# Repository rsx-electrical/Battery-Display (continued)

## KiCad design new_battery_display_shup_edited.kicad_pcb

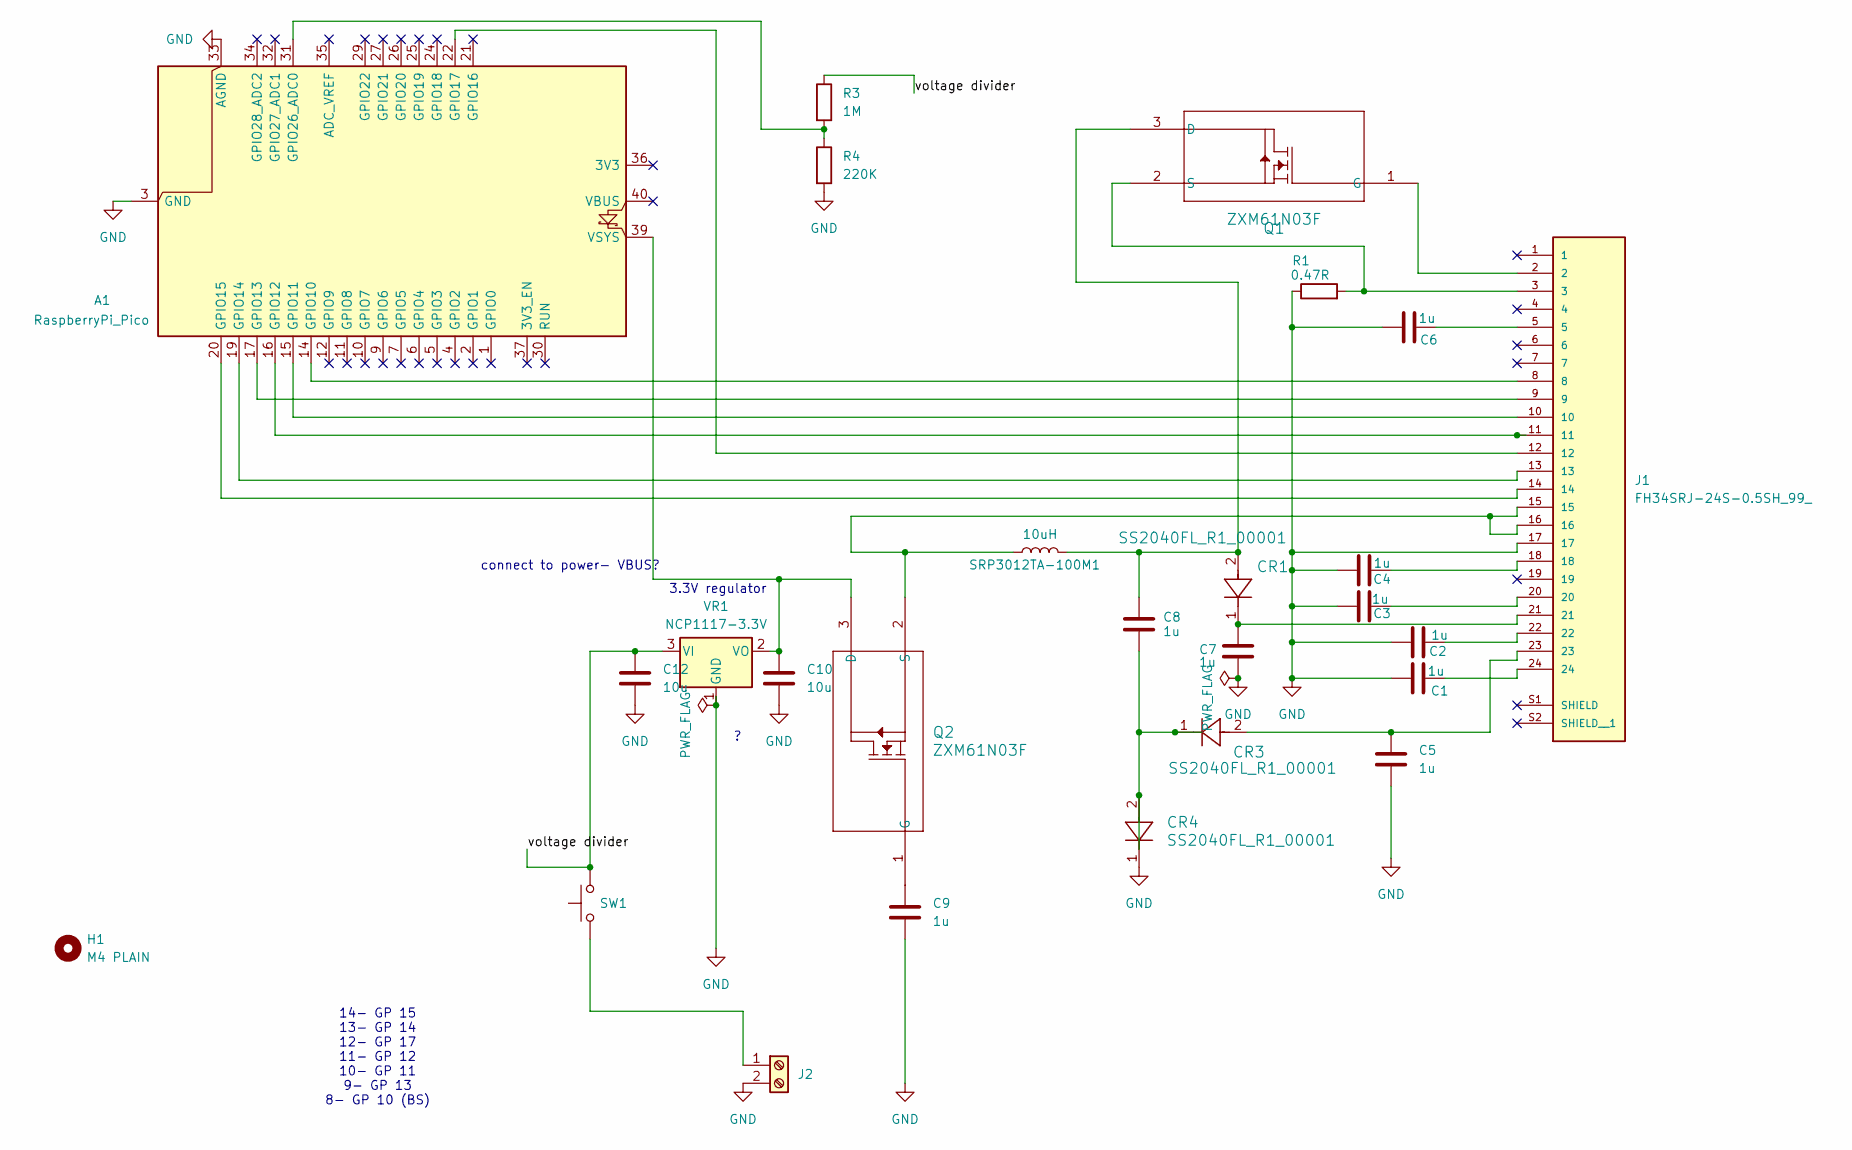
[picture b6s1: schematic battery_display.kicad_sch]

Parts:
A1: RaspberryPi_Pico; RaspberryPi_Pico_Common_Unspecified
C1, C2, C3, C4, C5, C6, C7, C8, C9: 1u; C_0805_2012Metric; MPN CL21B105KBFNNNE
C10, C12: 10u; C_0805_2012Metric; MPN GRM21BR61H106KE43L
CR1, CR3, CR4: SS2040FL_R1_00001; Nexperia_CFP3_SOD-123W; MPN SS2040FL_R1_00001
H1: M4 PLAIN; MountingHole_4.5mm
J1: FH34SRJ-24S-0.5SH_99_; HRS_FH34SRJ-24S-0.5SH_99_; PARTREV NA
J2: Screw_Terminal_2x2.54; Wurth_691210910002; MPN 691210910002
Q1, Q2: ZXM61N03F; SOT-23; MPN ZXM61N03FTA
R1: 0.47R; R_1206_3216Metric; MPN RL1206FR-070R47L
R3: 1M; R_0603_1608Metric; MPN ERJ-3EKF1004V
R4: 220K; R_0603_1608Metric; MPN RMCF0603FT220K
SRP3012TA-100M1: 10uH; IND_SRP3012TA_BRN; MPN SRP3012TA-100M
SW1: Button-THT - 2-1825910-7; 2-1825910-7; MPN 2-1825910-7
VR1: NCP1117-3.3V; SOT-223-3_TabPin2; MPN NCP1117IST33T3G

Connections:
/voltage divider: C12.1, R3.1, SW1.2, VR1.3 (VI)
GND: A1.3 (GND), A1.8 (GND), A1.13 (GND), A1.18 (GND), A1.23 (GND), A1.28 (GND), A1.33 (AGND), A1.38 (GND), C1.1, C2.1, C3.1, C4.1, C5.2, C6.1, C7.1, C9.1, C10.2, C12.2, CR4.1, J1.17, J2.2, R1.1, R4.2, VR1.1 (GND); also elsewhere on the board
unnamed: A1.14 (GPIO10), J1.8
unnamed: A1.15 (GPIO11), J1.10
unnamed: A1.16 (GPIO12), J1.11
unnamed: A1.17 (GPIO13), J1.9
unnamed: A1.19 (GPIO14), J1.13
unnamed: A1.20 (GPIO15), J1.14
unnamed: A1.22 (GPIO17), J1.12
unnamed: A1.31 (GPIO26_ADC0), R3.2, R4.1
unnamed: A1.39 (VSYS), C10.1, Q2.3 (D), VR1.2 (VO)
unnamed: C1.2, J1.24
unnamed: C2.2, J1.22
unnamed: C3.2, J1.20
unnamed: C4.2, J1.18
unnamed: C5.1, CR3.2, J1.23
unnamed: C6.2, J1.5
unnamed: C7.2, CR1.1, J1.21
unnamed: C8.1, CR3.1, CR4.2
unnamed: J2.1, SW1.1
unnamed 20: C8.2, CR1.2, Q1.3 (D), SRP3012TA-100M1.2; also elsewhere on the board
unnamed 21: J1.2, Q1.1 (G); also elsewhere on the board
unnamed: J1.3, Q1.2 (S), R1.2
unnamed: C9.2, Q2.1 (G)
unnamed: J1.15, J1.16, Q2.2 (S), SRP3012TA-100M1.1

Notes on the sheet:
3.3V regulator
connect to power- VBUS?
14- GP 15 13- GP 14 12- GP 17 11- GP 12 10- GP 11 9- GP 13 8- GP 10 (BS)

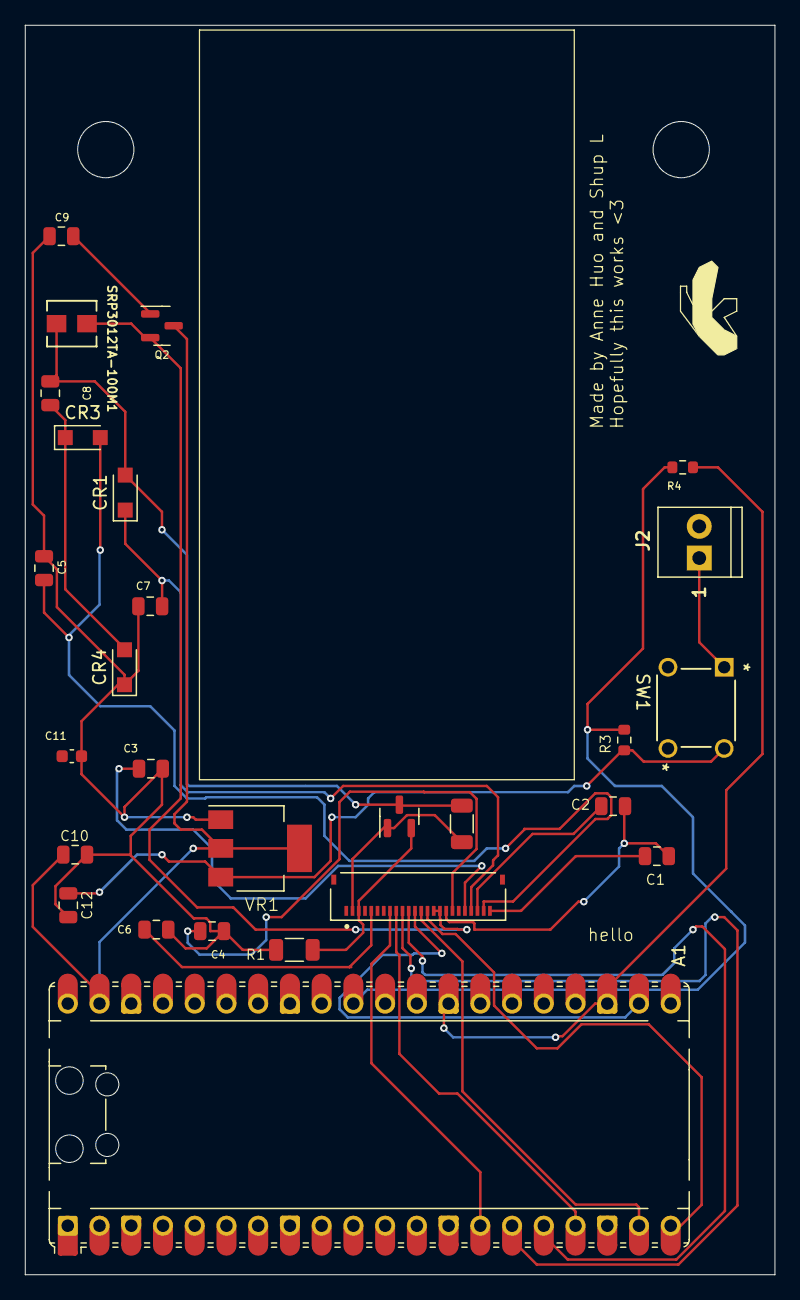
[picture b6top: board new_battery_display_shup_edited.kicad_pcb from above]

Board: 2 copper layers, 60.0 x 100.0 mm, 29 parts (0 on the bottom side), 25 nets.

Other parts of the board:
C11: 0u1; C_0603_1608Metric
H1#2: M4 PLAIN; MountingHole_4.5mm
R2: 0.47R; R_1206_3216Metric

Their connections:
GND: C11.2; also elsewhere on the board
unnamed 20: R2.1; also elsewhere on the board
unnamed 21: R2.2; also elsewhere on the board

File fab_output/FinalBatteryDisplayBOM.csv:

"Id";"Designator";"Footprint";"Quantity";"Designation";"Supplier and ref";
1;"C3,C5,C9,C8,C2,C6,C4,C1";"C_0805_2012Metric";8;"1u";;;
2;"J1";"HRS_FH34SRJ-24S-0.5SH_99_";1;"FH34SRJ-24S-0.5SH_99_";;;
3;"C10,C7";"C_0805_2012Metric";2;"10u";;;
4;"Q2";"SOT-23";1;"ZXM61N03F";;;
5;"R6";"R_0603_1608Metric";1;"249K_0.1%";;;
6;"C13";"C_0603_1608Metric";1;"0u1";;;
7;"R2";"R_1206_3216Metric";1;"0.47R";;;
8;"CR1,CR2,CR3";"Nexperia_CFP3_SOD-123W";3;"SS2040FL_R1_00001";;;
9;"VR1";"SOT-223-3_TabPin2";1;"NCP1117-3.3V";;;
10;"J2";"Wurth_691210910002";1;"Screw_Terminal_2x2.54";;;
11;"SW1";"FSMSMTR";1;"Button";;;
12;"I1-SRP";"IND_SRP3012TA_BRN";1;"10uH";;;
13;"A2";"RaspberryPi_Pico_Common_Unspecified";1;"RaspberryPi_Pico";;;
14;"C12";"C_0805_2012Metric";1;"4u7";;;
15;"R7";"R_0603_1608Metric";1;"1M";;;

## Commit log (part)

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2025-09-06 Created Shopping List
2025-09-06 Updated Shopping List Formmating
2025-09-16 add screen
2025-09-16 nmos
2025-09-16 alexmos
2025-09-24 add ldo
2025-09-28 shopping list 3v3 ldo
2025-10-04 add kicad project
2025-10-04 Started schematic
2025-10-04 EndofOct4
2025-10-11 Oct11_Schematic
2025-10-11 Add EPD library
2025-10-18 update schematic with 2 diodes
2025-10-18 display kicad schematic
2025-10-18 what the heklly
2025-10-18 2nd display
2025-10-18 added pico help
    asd
2025-10-18 display
2025-10-18 Create oct 18
2025-10-19 removed unnecessary mosfet in list
2025-10-19 Revert "removed unnecessary mosfet in list"
    This reverts commit 033c1a85e05191d0f7b3fb11770f73466afdf9e2.
2025-10-19 removed useless mosfet
2025-10-19 started battery display schematic
2025-10-19 Create fp-info-cache
2025-10-25 add button
2025-10-25 add button 2
2025-10-25 add pico pinout pic
2025-10-25 Schematic in progress
    added base schematic
    -next steps:
    -add connections to rpi pico
    -find values for soft start
2025-10-25 updated library links
2025-11-01 arduino w/ new components project folder added
2025-11-01 new project folders for new arduino and new comps vers
2025-11-01 Add progress so far
2025-11-01 Nano every
2025-11-01 Schematic with Pico
2025-11-01 Pico connected to display (mostly???)
2025-11-01 Display + Pico + voltage regulator
2025-11-08 Nov8 update
2025-11-08 11/08/25
2025-11-08 fixed
2025-11-08 title
2025-11-08 fixed changes
2025-11-08 new voltage regulator
2025-11-09 nov 8th changed back to raspberry pico
2025-11-15 i hate git: added voltage divider, added pwr flag
2025-11-15 added stuff:
    biuiuhiu
2025-11-15 Nov 15 schematic
2025-11-22 added new stuff:slow start
2025-11-22 remove op amp, used voltage divider with 1M resistor
2025-11-22 Nov22
2025-11-22 i made a new project titled yey. it is under the folder new_display
2025-11-22 Completed PCB Layout
    - also added voltage divider for reading voltage of the battery
    - next step ask coco for conformation
2025-11-29 Added some small fixes
    - moved stabilizing caps closer to cct
    - labelled orientation of rpi pico and screw terminal
    - changed 'Vcc" to "12-16V"
2026-01-02 Add files via upload
    updated files
    hopefully doesnt break
2026-01-02 Delete new_display/yey.kicad_pro
    change with updated one
2026-01-02 Add files via upload
    new pro file
2026-01-03 updated FPC connector choices
    possible cheaper option from wurst
2026-01-05 Revert "Added some small fixes"
    This reverts commit 59b639d84f345d5fabc6edbb6fa9331222a6e139.
2026-01-05 Reapply "Added some small fixes"
    This reverts commit d414565db0f35087673e5f9750bdaf74336bf2be.
2026-01-11 Jan10 Update
2026-01-17 Fixed drill hole placement
    Adjusted board layout to match drill placement with mech diagram.
    drill holes placed 7.5mm away from the edge of the display.
2026-01-17 Adjusted drill hole placements (again)
    Drill holes moved to be 30mm away from the left edge of the board
2026-01-17 changed wire connections
    changed back side wires to front side wires to avoid back side copper islanding
2026-01-17 actually made the changes in the previous 2 pushes
    💀
2026-01-17 Add files via upload
    newest changes
    meets reuqirements
2026-01-17 Moved the display connector closer to the RPi
2026-01-17 made some changes (idek what i changed)
    💀
2026-01-17 fixed traumatic errors
2026-01-17 Add files via upload
    i made stuff thicc af
2026-01-18 laid out pcb
2026-01-24 bill of materials
2026-01-24 Silk screen names
2026-01-31 update schematic
2026-01-31 fixed some errors
2026-01-31 organized final design files
2026-01-31 Drill, Gerber and BOM
2026-01-31 rename
2026-01-31 fab output folder
2026-01-31 Fixed some warnings
    - removed useless via and unconnected wire
2026-01-31 Fixed Position of drill holes to match E-Stop Drawing
2026-01-31 layout update
2026-01-31 update output files
2026-02-07 added gerbers and BOM
2026-02-07 adding BOM to git
2026-02-07 added bom
2026-02-07 finished routing, ready for submisison (files in folder titled 'submission')
2026-02-13 adding combined bom
2026-03-06 combined bom
2026-03-06 add zip
2026-05-16 add arduino code
2026-05-16 python code
2026-05-16 remove blinks
2026-05-17 revised
2026-05-20 PCB_Done
